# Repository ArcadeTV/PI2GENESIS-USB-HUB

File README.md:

# PI2GENESIS-USB-HUB

PCB for placing a RaspberryPi3 into Nerd Block's Genesis USB Hub and getting 15KHz RGB Video + CompositeSync out of it.

## What does it do, exactly?

Connects to a Raspberry PI 3(b) inside the housing of Arcadeblock(Nerdblock) Genesis USB Hub and turns it into a mini-videogame-system.
Video-Output is 15KHz-RGB. Needs configuration settings to output correct video. (Like/same as Pi2Scart or Pi2Jamma)
Uses the original USB-sockets from the USB-Hub's PCB.

## PCB Specs and getting hands on the boards
I can recommend itead.cc for pcb manufacturing. Either export the GERBER files from EAGLE using the files that I provided or wait until I finished writing this readme and find them inside the repository.
```
### PCB SPECS:
----------------
* 10.0 x 5.0 cm
* 1.2 mm Thickness
* Surface: HASL
```

### Installing

```
I made a PDF with an installation guide.
```
* desolder original USB-sockets and install them on the pcb
* solder PCB to GPIO-pins
* connect usb-pins with cables (D+ and D- Lines 1-4)
* connect usb-power-pin to one of the usb-sockets on the PI
* connect AUDIO from PI to SND-L and SND-R pins
* connect VIDEO-OUT to AV-Socket
* connect POWER and GND from PSU to 5V-IN
* connect POWER and GND from 5V-OUT to PI-Power-Input (miniUSB-port)
* when AUDIO has noise, use a groundloop-isolator between the connetction

## Additional Modding of the Hub's case

* DC-Power-Input (5V)
* Video-Out via 8-Pin-MiniDIN Socket (I also provided files for a convenient adapter)
* optional separate H- and V-Sync via dedicated cinch-sockets and cinch-to-bnc cables for studio monitors/PVM

## On the Software-Side

Search the web for GertVGA66, PI2SCART, PI2JAMMA and similar Projects. Once your PI is configured to output video through the GPIO port, the built-in DAC on the PCB will produce 15KHz RGB Video.

## Built With

* EAGLE (https://www.autodesk.de/products/eagle/overview)

## Versioning

This is likely the first and last release of this project.

## Authors

* **Alex Schütz**

## License

This project is licensed under the MIT License - see the [LICENSE.md](LICENSE.md) file for details

## Acknowledgments

* This project is completely UNTESTED!
* Inspiration came from GERT/VGA666 and other Pi2RGB Projects
* Please don't mess with electronics if you have no clue what you're doing!

## Q&A's

* Why did you abandon this project?

-> The USB-hubs are sold out and I have other stuff to care about.

* Why is the Raspberry Pi's sound so bad over the headphone jack?

-> It's because of the PI's limitations regarding analogue sound. Get a USB-Soundcard! Those are dirtcheap and produce very acceptable audio.

* Can I still use HDMI as Video-Output?

-> Sure, but then I suggest you just pass installing this pcb, it will not get you any advantage while using HDMI.

* Man, I love your stuff - Can you please send me a fully loaded pcb because I have 2 left hands and can't solder.

-> Dude, just download the stuff that I release to the public. It usually contains everything you need to order PCBs wherever you want plus information on how to use or install it. Anyways, if you can't solder, sending you a pupulated PCB is like sending you a can, knowing you don't have a can-opener...

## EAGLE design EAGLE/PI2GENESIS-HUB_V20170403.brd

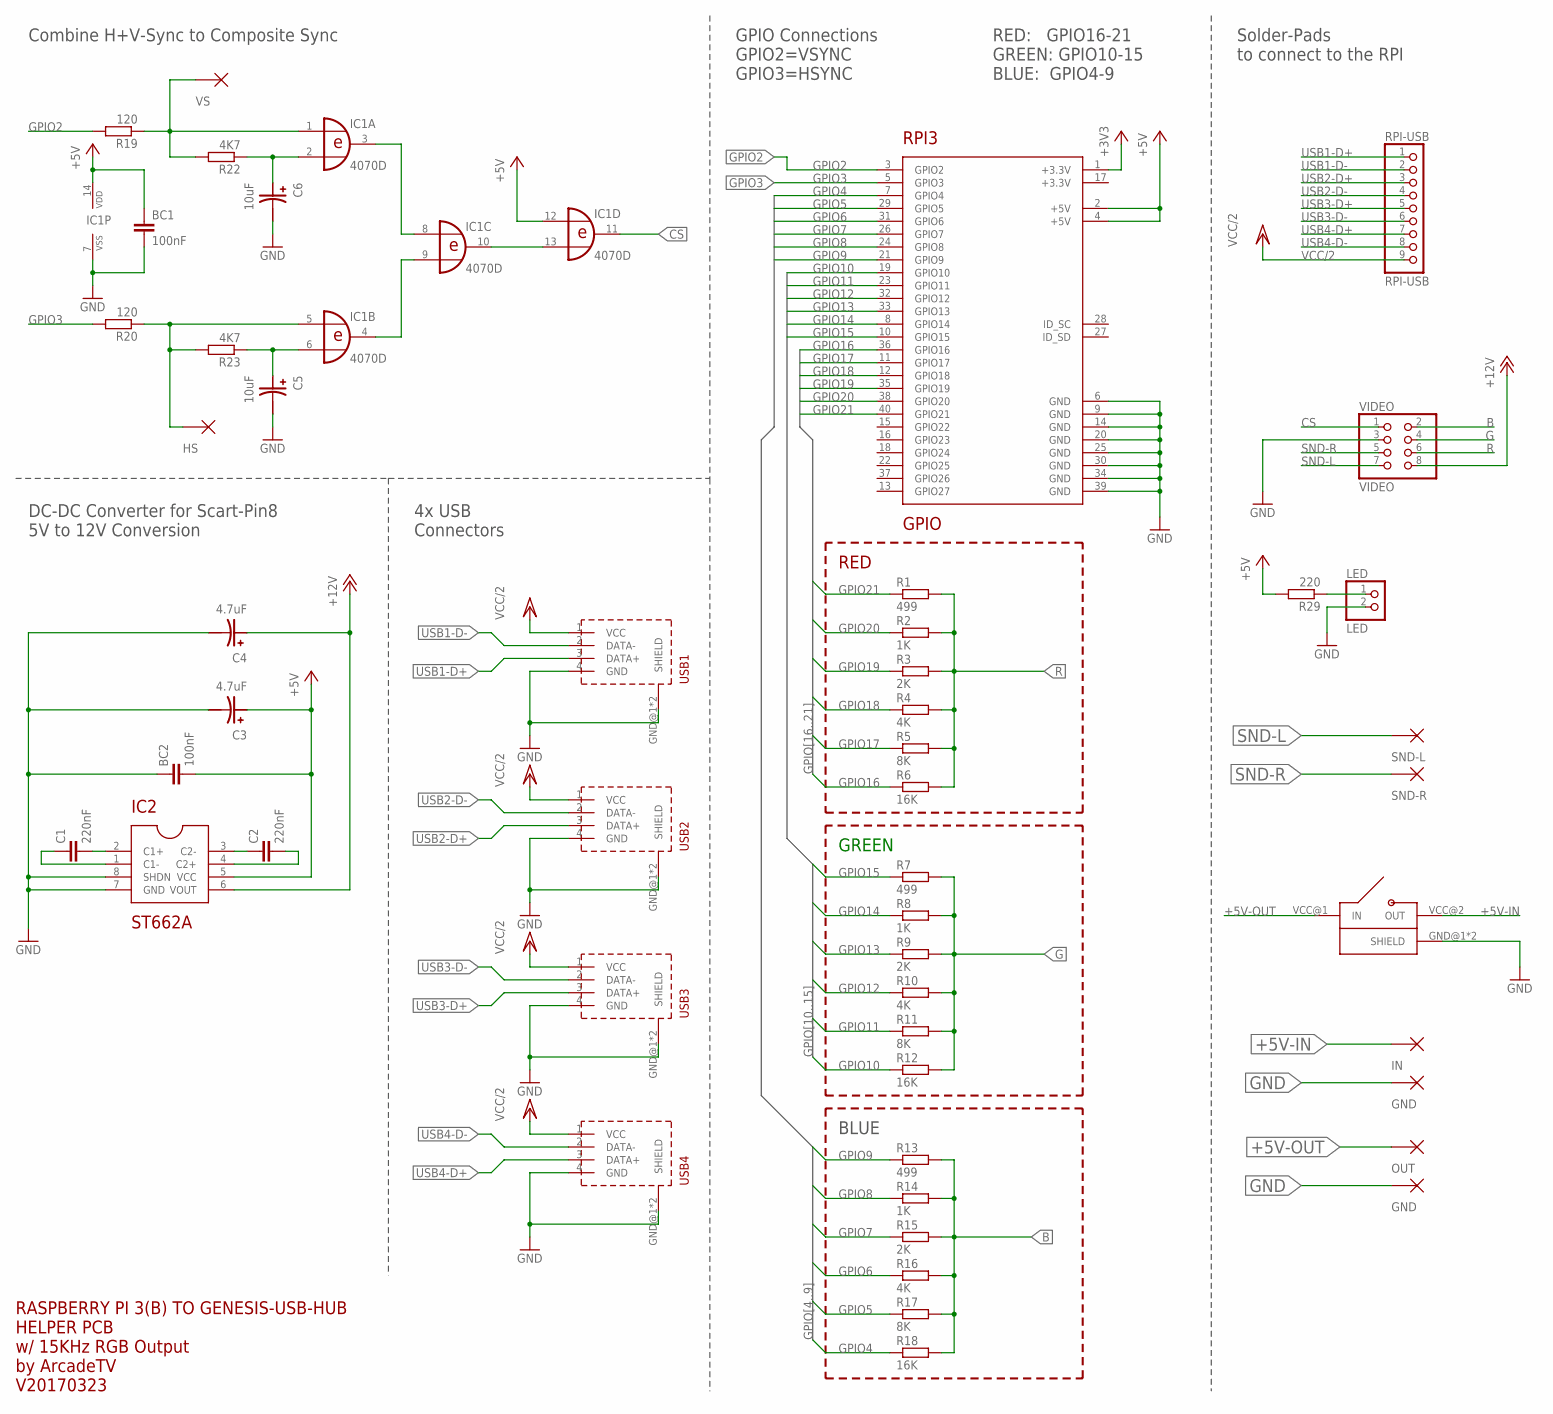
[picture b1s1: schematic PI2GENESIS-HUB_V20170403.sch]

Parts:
BC1, BC2: 100nF; Z0805
C1, C2: 220nF; Z0805
C3, C4: 4.7uF; EEEFPJ101UAR_PANASONIC_VFP-SERIES
C5, C6: 10uF; EEEFPJ101UAR_PANASONIC_VFP-SERIES
IC1: 4070D; SO14
IC2: ST662A; SO-8
LED: LED; 1X02
PAD1: HS; PADS
PAD2: VS; PADS
R1, R7, R13: 499; Z0805
R2, R8, R14: 1K; Z0805
R3, R9, R15: 2K; Z0805
R4, R10, R16: 4K; Z0805
R5, R11, R17: 8K; Z0805
R6, R12, R18: 16K; Z0805
R19, R20: 120; Z0805
R22, R23: 4K7; Z0805
R29: 220; Z0805
RPI3: GPIO; RPI3-GPIO
RPI-USB: RPI-USB; 1X09
U$1: OUT; PADS
U$2: SND-L; PADS
U$3: SND-R; PADS
U$4: ALPS-SSSU011700
U$5: IN; PADS
U$6, U$7: GND; PADS
USB1, USB2, USB3, USB4: USB-GENESIS-HUB
VIDEO: VIDEO; 2X04

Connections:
+3V3: RPI3.1 (+3.3V)
+5V: BC1.1, BC2.2, C3.PLUS (+), IC1.12 (I0), IC1.14 (VDD), IC2.5 (VCC), R29.2, RPI3.2 (+5V), RPI3.4 (+5V)
+5V-IN: U$4.VCC@2 (OUT), U$5.P$1
+5V-OUT: U$1.P$1, U$4.VCC@1 (IN)
+12V: C4.PLUS (+), IC2.6 (VOUT), VIDEO.8
B: R13.2, R14.2, R15.2, R16.2, R17.2, R18.2, VIDEO.2
CS: IC1.11 (O), VIDEO.1
G: R7.2, R8.2, R9.2, R10.2, R11.2, R12.2, VIDEO.4
GND: BC1.2, BC2.1, C3.MINUS (-), C4.MINUS (-), C5.MINUS (-), C6.MINUS (-), IC1.7 (VSS), IC2.7 (GND), IC2.8 (SHDN), LED.2, RPI3.6 (GND), RPI3.9 (GND), RPI3.14 (GND), RPI3.20 (GND), RPI3.25 (GND), RPI3.30 (GND), RPI3.34 (GND), RPI3.39 (GND), U$4.GND@1 (SHIELD), U$4.GND@2 (SHIELD), U$6.P$1, U$7.P$1, USB1.4 (GND), USB1.GND@1 (SHIELD), USB1.GND@2 (SHIELD), USB2.4 (GND), USB2.GND@1 (SHIELD), USB2.GND@2 (SHIELD), USB3.4 (GND), USB3.GND@1 (SHIELD), USB3.GND@2 (SHIELD), USB4.4 (GND), USB4.GND@1 (SHIELD), USB4.GND@2 (SHIELD), VIDEO.3
GPIO2: R19.2, RPI3.3 (GPIO2)
GPIO3: R20.2, RPI3.5 (GPIO3)
GPIO4: R18.1, RPI3.7 (GPIO4)
GPIO5: R17.1, RPI3.29 (GPIO5)
GPIO6: R16.1, RPI3.31 (GPIO6)
GPIO7: R15.1, RPI3.26 (GPIO7)
GPIO8: R14.1, RPI3.24 (GPIO8)
GPIO9: R13.1, RPI3.21 (GPIO9)
GPIO10: R12.1, RPI3.19 (GPIO10)
GPIO11: R11.1, RPI3.23 (GPIO11)
GPIO12: R10.1, RPI3.32 (GPIO12)
GPIO13: R9.1, RPI3.33 (GPIO13)
GPIO14: R8.1, RPI3.8 (GPIO14)
GPIO15: R7.1, RPI3.10 (GPIO15)
GPIO16: R6.1, RPI3.36 (GPIO16)
GPIO17: R5.1, RPI3.11 (GPIO17)
GPIO18: R4.1, RPI3.12 (GPIO18)
GPIO19: R3.1, RPI3.35 (GPIO19)
GPIO20: R2.1, RPI3.38 (GPIO20)
GPIO21: R1.1, RPI3.40 (GPIO21)
unnamed: C1.2, IC2.2 (C1+)
unnamed: C1.1, IC2.1 (C1-)
unnamed: C2.1, IC2.3 (C2-)
unnamed: C2.2, IC2.4 (C2+)
unnamed: LED.1, R29.1
unnamed: IC1.1 (I0), PAD2.P$1, R19.1, R22.2
unnamed: C5.PLUS (+), IC1.6 (I1), R23.1
unnamed: IC1.4 (O), IC1.9 (I1)
unnamed: IC1.10 (O), IC1.13 (I1)
unnamed: IC1.5 (I0), PAD1.P$1, R20.1, R23.2
unnamed: IC1.3 (O), IC1.8 (I0)
unnamed: C6.PLUS (+), IC1.2 (I1), R22.1
R: R1.2, R2.2, R3.2, R4.2, R5.2, R6.2, VIDEO.6
SND-L: U$2.P$1, VIDEO.7
SND-R: U$3.P$1, VIDEO.5
USB1-D+: RPI-USB.1, USB1.3 (DATA+)
USB1-D-: RPI-USB.2, USB1.2 (DATA-)
USB2-D+: RPI-USB.3, USB2.3 (DATA+)
USB2-D-: RPI-USB.4, USB2.2 (DATA-)
USB3-D+: RPI-USB.5, USB3.3 (DATA+)
USB3-D-: RPI-USB.6, USB3.2 (DATA-)
USB4-D+: RPI-USB.7, USB4.3 (DATA+)
USB4-D-: RPI-USB.8, USB4.2 (DATA-)
VCC/2: RPI-USB.9, USB1.1 (VCC), USB2.1 (VCC), USB3.1 (VCC), USB4.1 (VCC)

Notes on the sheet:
DC-DC Converter for Scart-Pin8 5V to 12V Conversion
4x USB Connectors
GPIO Connections GPIO2=VSYNC GPIO3=HSYNC
RED
GREEN
BLUE
RED: GPIO16-21 GREEN: GPIO10-15 BLUE: GPIO4-9
Combine H+V-Sync to Composite Sync
RASPBERRY PI 3(B) TO GENESIS-USB-HUB HELPER PCB w/ 15KHz RGB Output by ArcadeTV V20170323
Solder-Pads to connect to the RPI

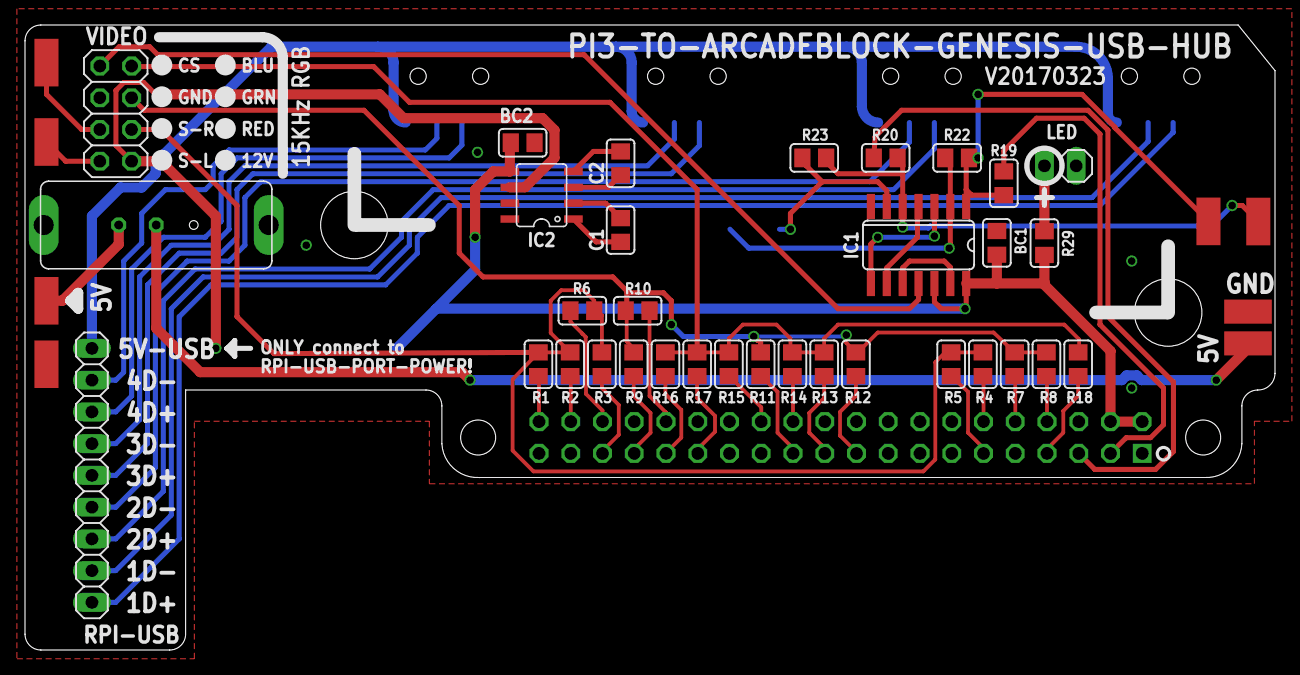
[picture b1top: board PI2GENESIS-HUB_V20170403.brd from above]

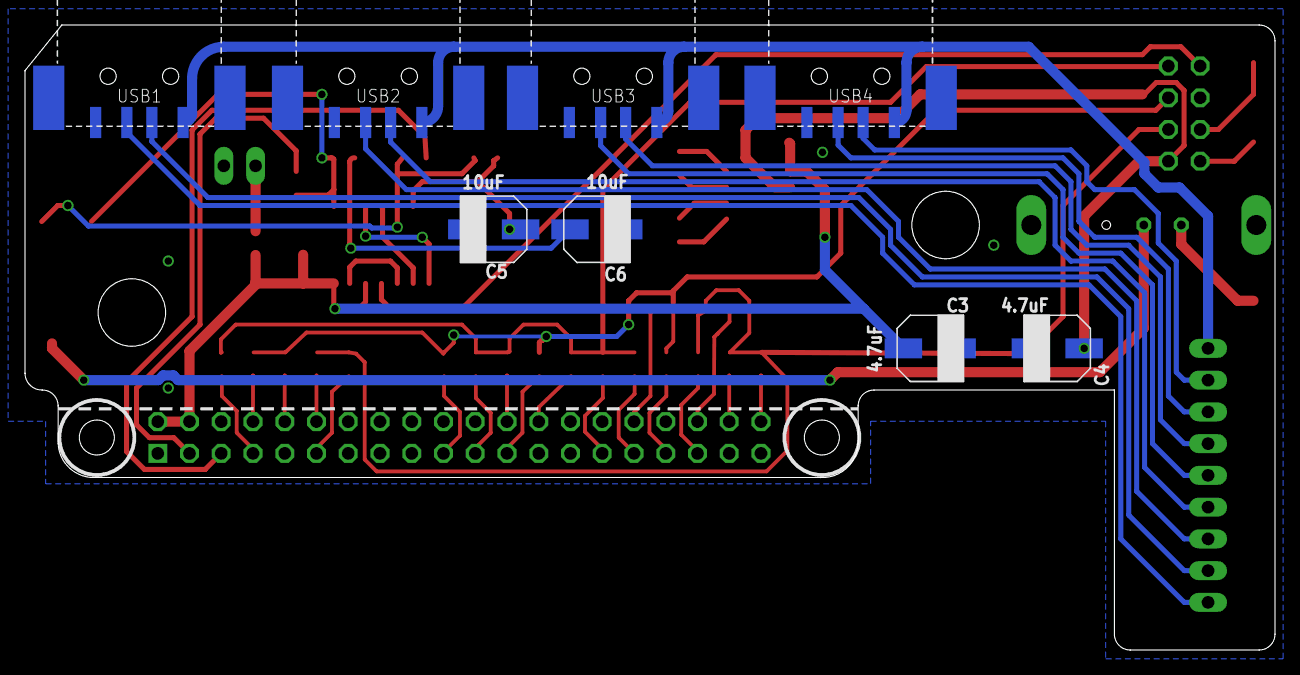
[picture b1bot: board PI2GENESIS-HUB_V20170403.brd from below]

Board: 2 copper layers, 100.0 x 50.0 mm, 50 parts (9 on the bottom side), 52 nets.

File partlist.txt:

Partlist

Exported from PI2GENESIS-HUB_SWITCH.sch at 22.03.17 22:21

EAGLE Version 8.1.0 Copyright (c) 1988-2017 Autodesk, Inc.

Assembly variant:

Part     Value           Device                            Package                           Library  Sheet

BC1      100nF           C0805                             Z0805                             arcadetv 1
BC2      100nF           C0805                             Z0805                             arcadetv 1
C1       220nF           C0805                             Z0805                             arcadetv 1
C2       220nF           C0805                             Z0805                             arcadetv 1
C3       4.7uF           EEEFPJ101UAR_PANASONIC_VFP-SERIES EEEFPJ101UAR_PANASONIC_VFP-SERIES arcadetv 1
C4       4.7uF           EEEFPJ101UAR_PANASONIC_VFP-SERIES EEEFPJ101UAR_PANASONIC_VFP-SERIES arcadetv 1
C5       10uF            EEEFPJ101UAR_PANASONIC_VFP-SERIES EEEFPJ101UAR_PANASONIC_VFP-SERIES arcadetv 1
C6       10uF            EEEFPJ101UAR_PANASONIC_VFP-SERIES EEEFPJ101UAR_PANASONIC_VFP-SERIES arcadetv 1
IC1      4070D           4070D                             SO14                              40xx     1
IC2      ST662A          ST662A                            SO-8                              arcadetv 1
R1       499             R-US_R0603                        R0603                             rcl      1
R2       1K              R-US_R0603                        R0603                             rcl      1
R3       2K              R-US_R0603                        R0603                             rcl      1
R4       4K              R-US_R0603                        R0603                             rcl      1
R5       8K              R-US_R0603                        R0603                             rcl      1
R6       16K             R-US_R0603                        R0603                             rcl      1
R7       499             R-US_R0603                        R0603                             rcl      1
R8       1K              R-US_R0603                        R0603                             rcl      1
R9       2K              R-US_R0603                        R0603                             rcl      1
R10      4K              R-US_R0603                        R0603                             rcl      1
R11      8K              R-US_R0603                        R0603                             rcl      1
R12      16K             R-US_R0603                        R0603                             rcl      1
R13      499             R-US_R0603                        R0603                             rcl      1
R14      1K              R-US_R0603                        R0603                             rcl      1
R15      2K              R-US_R0603                        R0603                             rcl      1
R16      4K              R-US_R0603                        R0603                             rcl      1
R17      8K              R-US_R0603                        R0603                             rcl      1
R18      16K             R-US_R0603                        R0603                             rcl      1
R19      120             R-US_R0603                        R0603                             rcl      1
R20      120             R-US_R0603                        R0603                             rcl      1
R22      4K7             R-US_R0603                        R0603                             rcl      1
R23      4K7             R-US_R0603                        R0603                             rcl      1
R29      220             R-US_R0603                        R0603                             rcl      1
U$4      ALPS-SSSU011700 ALPS-SSSU011700                   ALPS-SSSU011700                   arcadetv 1

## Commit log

2017-07-18 Rename PI2GENESIS-HUB_V20170403.GBL to GERBERS/PCB/PI2GENESIS-HUB_V20170403.GBL
2017-07-18 Rename PI2GENESIS-HUB_V20170403.GBO to GERBERS/PCB/PI2GENESIS-HUB_V20170403.GBO
2017-07-18 Rename PI2GENESIS-HUB_V20170403.GBS to GERBERS/PCB/PI2GENESIS-HUB_V20170403.GBS
2017-07-18 Rename PI2GENESIS-HUB_V20170403.GKO to GERBERS/PCB/PI2GENESIS-HUB_V20170403.GKO
2017-07-18 Rename PI2GENESIS-HUB_V20170403.GTL to GERBERS/PCB/PI2GENESIS-HUB_V20170403.GTL
2017-07-18 Rename PI2GENESIS-HUB_V20170403.GTO to GERBERS/PCB/PI2GENESIS-HUB_V20170403.GTO
2017-07-18 Rename PI2GENESIS-HUB_V20170403.GTS to GERBERS/PCB/PI2GENESIS-HUB_V20170403.GTS
2017-07-18 Rename PI2GENESIS-HUB_V20170403.TXT to GERBERS/PCB/PI2GENESIS-HUB_V20170403.TXT
2017-07-18 Rename md80sv_adapter.GBL to GERBERS/VIDEO-ADAPTER/md80sv_adapter.GBL
2017-07-18 Rename md80sv_adapter.GBO to GERBERS/VIDEO-ADAPTER/md80sv_adapter.GBO
2017-07-18 Rename md80sv_adapter.GBS to GERBERS/VIDEO-ADAPTER/md80sv_adapter.GBS
2017-07-18 Rename md80sv_adapter.GKO to GERBERS/VIDEO-ADAPTER/md80sv_adapter.GKO
2017-07-18 Rename md80sv_adapter.GTL to GERBERS/VIDEO-ADAPTER/md80sv_adapter.GTL
2017-07-18 Rename md80sv_adapter.GTO to GERBERS/VIDEO-ADAPTER/md80sv_adapter.GTO
2017-07-18 Rename md80sv_adapter.GTS to GERBERS/VIDEO-ADAPTER/md80sv_adapter.GTS
2017-07-18 Rename md80sv_adapter.TXT to GERBERS/VIDEO-ADAPTER/md80sv_adapter.TXT
2017-07-18 Rename PI2GENESIS-HUB_V20170403.brd to EAGLE/PI2GENESIS-HUB_V20170403.brd
2017-07-18 Rename PI2GENESIS-HUB_V20170403.sch to EAGLE/PI2GENESIS-HUB_V20170403.sch
2017-07-18 Rename md80sv_adapter.brd to EAGLE/md80sv_adapter.brd
2017-07-18 Rename md80sv_adapter.sch to EAGLE/md80sv_adapter.sch
